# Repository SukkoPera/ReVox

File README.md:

# ReVox
ReVox is an Open Hardware sound card that adds a Digital-to-Analog Converter (DAC) to the Commodore 16, 116 and Plus/4 home computers.

## Summary
The project was born from [an idea by Spektro](https://plus4world.powweb.com/forum/46186) to get his [Covox Speech Thing](https://en.wikipedia.org/wiki/Covox_Speech_Thing) working on his Plus/4. While I was trying to help him, I found [Yeo Kheng Meng's Speech Thing reimplementation](https://github.com/yeokm1/pcb-covox-amp) and decided to derive a C16/C116/+4 cartridge from it, since it looked pretty easy and the complete board would be usable on the C16/C116 as well (Initial attempts were aimed at connecting it to the User Port, which only the Plus/4 has and which does not even feature an audio input pin).

The outcome is a a very cheap board (it can probably be built with <10€ in components) that gives the C16/C116/+4 the ability to play sound samples with good quality. It is compatible with Solder/Synergy's [Digi-Blaster](https://plus4world.powweb.com/hardware/Digi-Blaster) and thus it can be used with all the (little, to be honest) [software that supports it](https://plus4world.powweb.com/effects/Digi-Blaster_support).

## Programming
ReVox has no buffer, which means it must be fed audio samples in real-time. This is not a trivial task and existing software should be analyzed in order to learn the best techniques to do so.

Sample data must be written to the same address as the Digi-Blaster, i.e.: $FD5E or $FE9E.

## Design and Assembly Notes
The board uses a [Resistor Ladder DAC](https://en.wikipedia.org/wiki/Resistor_ladder#R%E2%80%932R_resistor_ladder_network_(digital_to_analog_conversion)) which requires a bunch of resistors of some value (R) and another bunch of exactly twice that value (2R). While the exact values used are not too critical, in order to get the best sound out of it, it is imperative that *accurate* resistors are used. Now, don't be paranoid, **1% will be more than enough** and since anything in the 1k-100k range is probably fine, you can easily find something at a decent price. For instance, I used [MFR-25FTE52-11K](https://www.mouser.it/ProductDetail/YAGEO/MFR-25FTE52-11K?qs=oAGoVhmvjhw%252BYyqfPO08%252Bg%3D%3D) and [MFR-25FTE52-22K](https://www.mouser.it/ProductDetail/YAGEO/MFR-25FTE52-22K?qs=oAGoVhmvjhy9HBN%252Bz%2FOCyQ%3D%3D): you can get 100 of each for under 4€ and those will be enough to build at least 10 boards :).

Capacitor C3 introduces a low-pass filter at the DAC output: the value I used is 1.8nF but this was chosen "by ear", not by calculations. Feel free to try different values to your liking, in the 470pF-10nF range. Note that the value also depends on those of the resistors used in the ladder, so if you change those, you will need to change this one just as well.

The audio output is automatically fed back into the computer through the EXT_AUDIO pin, so that you will hear it mixed with the sounds produced by the TED. This might need some amplification, depending on the values of the resistors used, thus the board features an amplifier with configurable gain in order to bring the volume to an acceptable level. The original design uses a TLC272 (just because I had some laying around) but any other amplifier can be used with little modifications (which are up to you). One other I tested is LMC6482, with which R17 and R18 can be set to the same value (I used the same 11k resistors I used in the ladder), as it is a rail-to-rail model.

Actually not much amplification is needed with the 11/22K resistors. In fact, the JP1 jumper on the back of the board allows to completely bypass the amplifier, just in case: set it to RAW for bypassing or to AMP otherwise.

There is also a 3.5" jack connector on the board, which allows bringing the raw output of the DAC (and low-pass filter) to external equipment. Note that when a jack is plugged in, the DAC output will no longer be redirected to the EXT_AUDIO pin.

## Testing
I suggest to use [WavePlay-SD](https://plus4world.powweb.com/software/WavePlay-SD), a great piece of software that plays music with superb quality. Enter the Setup menu with <kbd>CTRL+S</kbd> and select *INT. INTL DGB:0* using the *MOD* button.

## License
The ReVox documentation, including the design itself, is copyright &copy; SukkoPera 2023 and is licensed under the [Creative Commons Attribution-NonCommercial-ShareAlike 4.0 International License](https://creativecommons.org/licenses/by-nc-sa/4.0/).

This documentation is distributed *as is* and WITHOUT ANY EXPRESS OR IMPLIED WARRANTIES whatsoever with respect to its functionality, operability or use, including, without limitation, any implied warranties OF MERCHANTABILITY, SATISFACTORY QUALITY, FITNESS FOR A PARTICULAR PURPOSE or infringement. We expressly disclaim any liability whatsoever for any direct, indirect, consequential, incidental or special damages, including, without limitation, lost revenues, lost profits, losses resulting from business interruption or loss of data, regardless of the form of action or legal theory under which the liability may be asserted, even if advised of the possibility or likelihood of such damages.

## Support the Project
If you want to get some boards manufactured, you can get them from PCBWay through this link:

You get my gratitude and cheap, professionally-made and good quality PCBs, I get some credit that will help with this and [other projects](https://www.pcbway.com/project/member/?bmbno=72D33927-5EF6-42). You won't even have to worry about the various PCB options, it's all pre-configured for you!

Also, if you still have to register, [you can use this link](https://www.pcbway.com/setinvite.aspx?inviteid=41100) to get some bonus initial credit (and yield me some more).

You can also buy me a coffee if you want, all the money collected this way will actually go to charity:

## Thanks
* Spektro for the original idea.
* Yeo Kheng Meng for his Speech Thing reimplementation.
* MMS, BSZ and all the other folks at the [Plus/4 World Forum](https://plus4world.powweb.com/forum) for help and advice.

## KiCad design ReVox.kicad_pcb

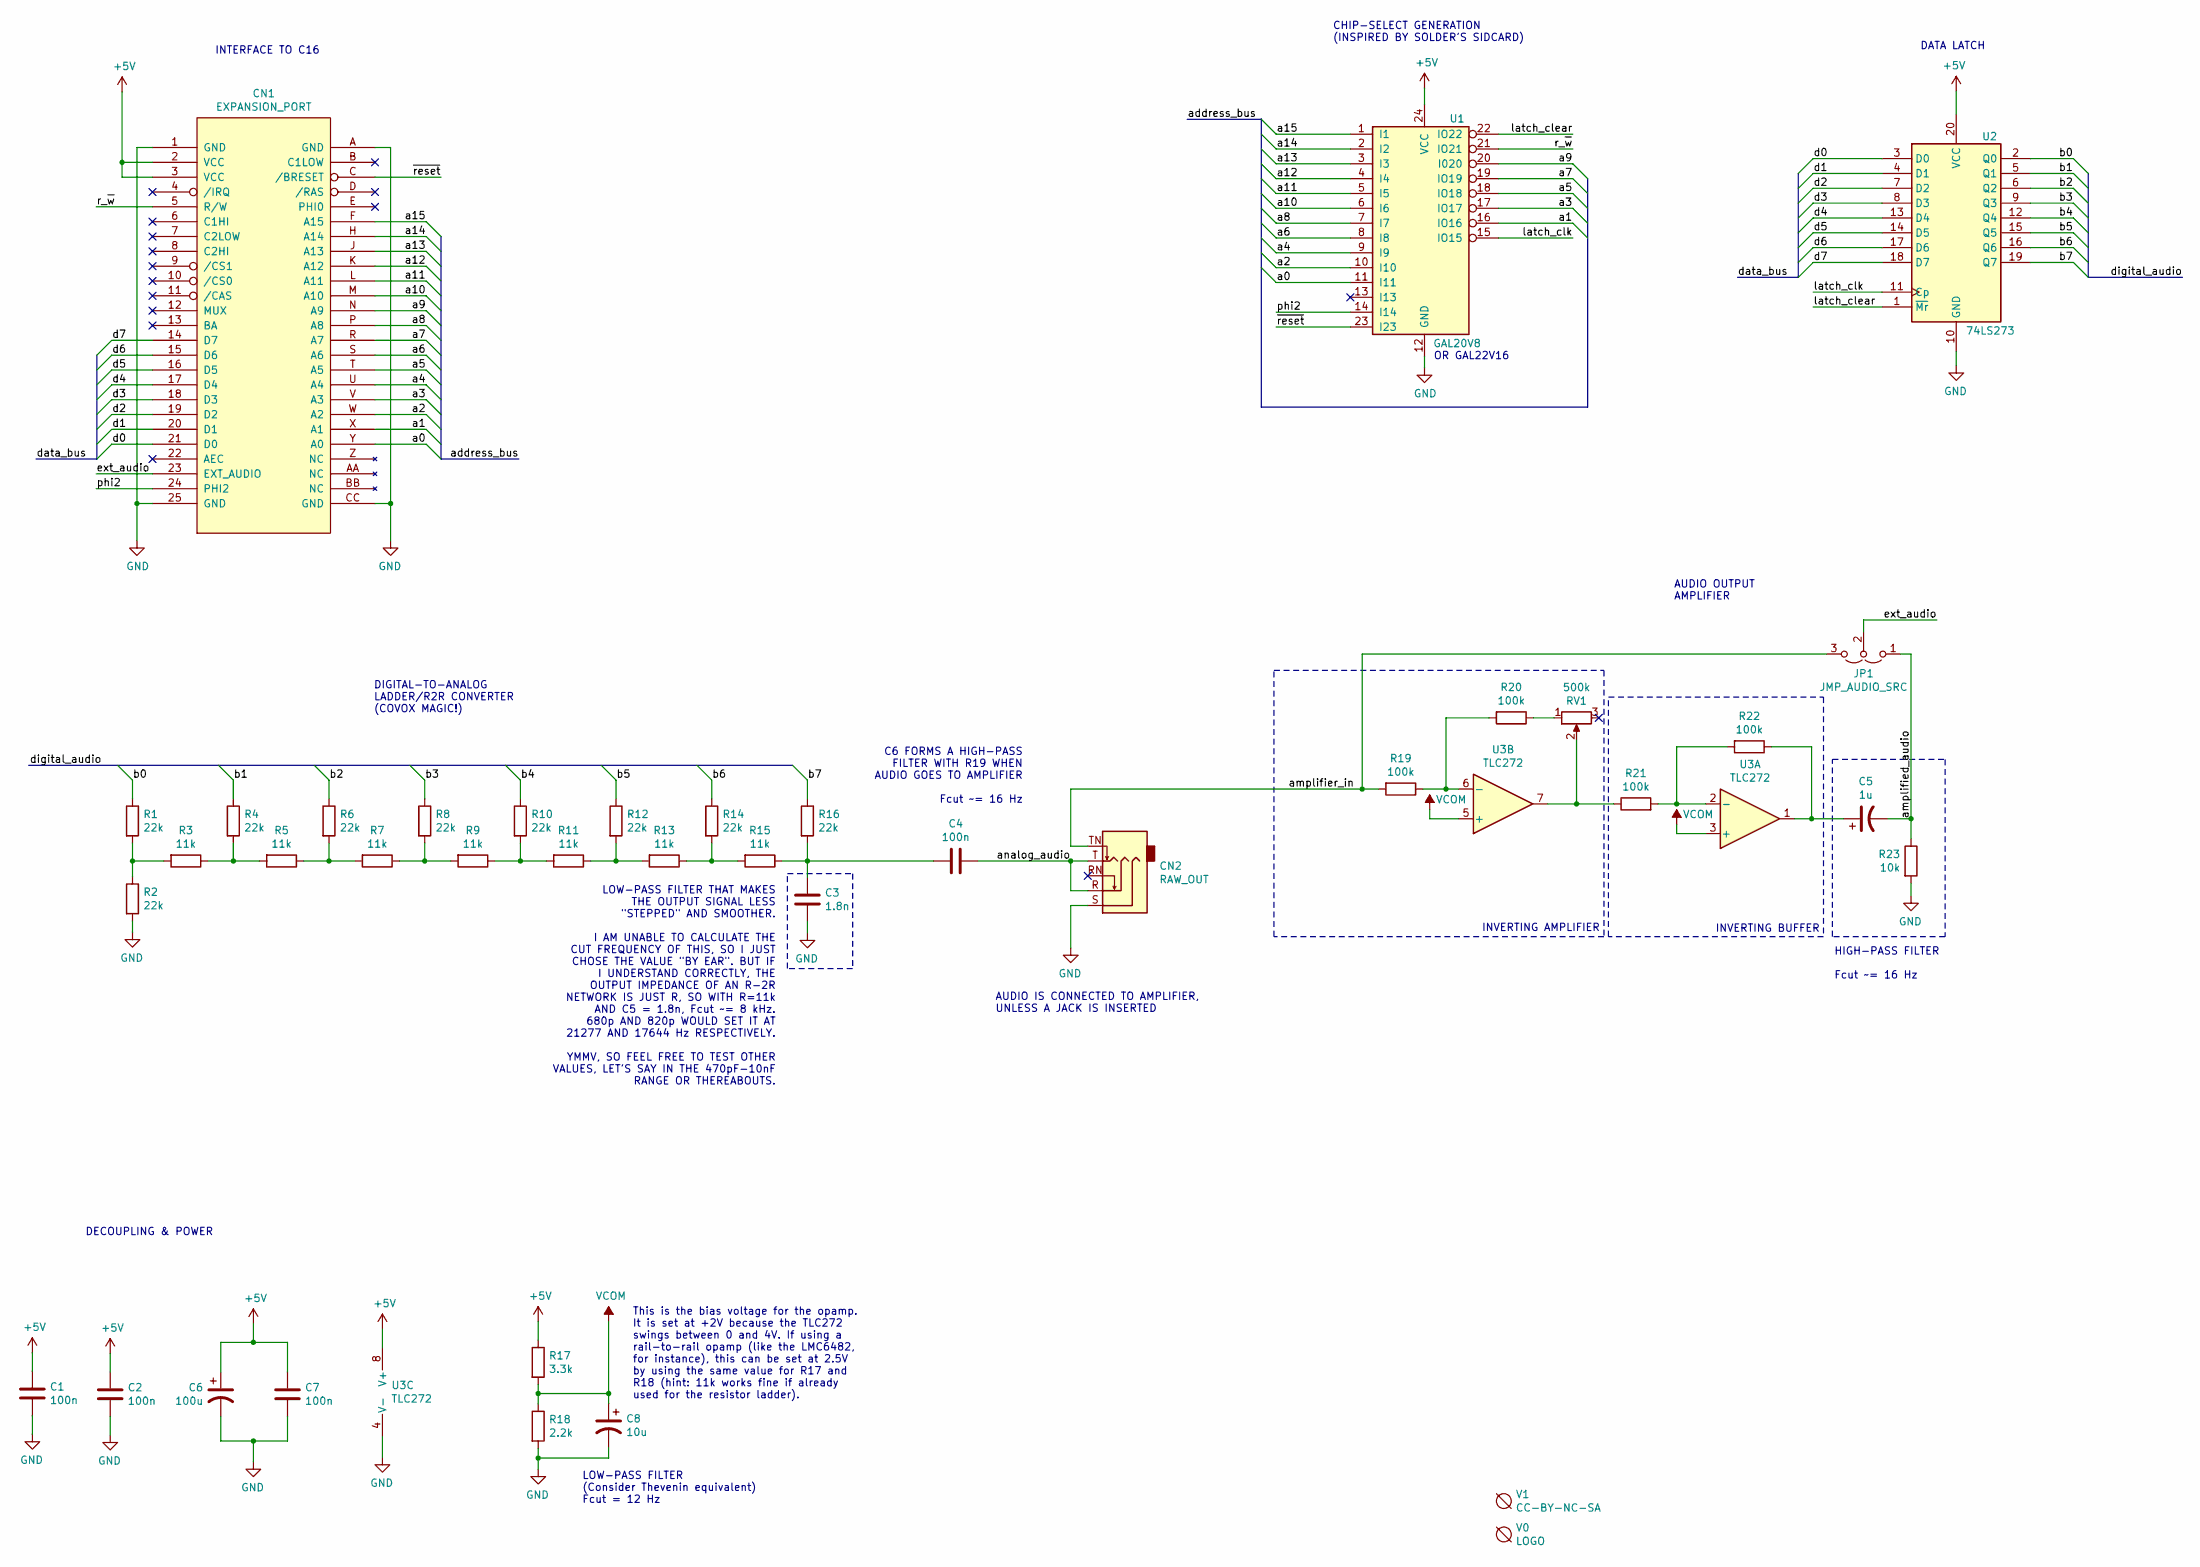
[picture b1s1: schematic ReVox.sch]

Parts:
C1, C2, C4, C7: 100n; C_Disc_D7.0mm_W2.5mm_P5.00mm; MouserPN 810-FG28X7R1H104KNT0
C3: 1.8n; C_Disc_D7.0mm_W2.5mm_P5.00mm; MouserPN 810-FG28X7R1H103KNT6
C5: 1u; CP_Radial_D5.0mm_P2.00mm; MouserPN 710-860010672005
C6: 100u; CP_Radial_D6.3mm_P2.50mm; MouserPN 710-860020573008
C8: 10u; CP_Radial_D5.0mm_P2.00mm; MouserPN 710-860010572002
CN1: EXPANSION_PORT; C16_Cart_Conn
CN2: RAW_OUT; AudioJack_SJ1-3525N; MouserPN 490-SJ1-3525N
JP1: JMP_AUDIO_SRC; SolderJumper-3_P1.3mm_Open_RoundedPad1.0x1.5mm
R1, R2, R4, R6, R8, R10, R12, R14, R16: 22k; R_Axial_DIN0207_L6.3mm_D2.5mm_P10.16mm_Horizontal; MouserPN 603-MFR-25FTE52-22K
R3, R5, R7, R9, R11, R13, R15: 11k; R_Axial_DIN0207_L6.3mm_D2.5mm_P10.16mm_Horizontal; MouserPN 603-MFR-25FTE52-11K
R17: 3.3k; R_Axial_DIN0207_L6.3mm_D2.5mm_P10.16mm_Horizontal
R18: 2.2k; R_Axial_DIN0207_L6.3mm_D2.5mm_P10.16mm_Horizontal
R19, R20, R21, R22: 100k; R_Axial_DIN0207_L6.3mm_D2.5mm_P10.16mm_Horizontal; MouserPN 603-MFR-25FTE52-11K
R23: 10k; R_Axial_DIN0207_L6.3mm_D2.5mm_P10.16mm_Horizontal; MouserPN 603-MFR-25FTE52-11K
RV1: 500k; Pot_Bourns_3306P; MouserPN 652-3306P-1-504
U1: GAL20V8; DIP-24_W7.62mm_Socket_LongPads; MouserPN 556-AF22LV10CQZ-30PU
U2: 74LS273; DIP-20_W7.62mm_Socket_LongPads; MouserPN 595-SN74HCT273N
U3: TLC272; DIP-8_W7.62mm_Socket_LongPads; MouserPN 595-TLC272BIP
V0: LOGO; logo
V1: CC-BY-NC-SA; cc_by_nc_sa

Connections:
+5V: C1.1, C2.1, C6.1, C7.1, CN1.2 (VCC), CN1.3 (VCC), R17.1, U1.24 (VCC), U2.20 (VCC), U3.8 (V+)
/a0: CN1.Y (A0), U1.11 (I11)
/a1: CN1.X (A1), U1.16 (IO16)
/a2: CN1.W (A2), U1.10 (I10)
/a3: CN1.V (A3), U1.17 (IO17)
/a4: CN1.U (A4), U1.9 (I9)
/a5: CN1.T (A5), U1.18 (IO18)
/a6: CN1.S (A6), U1.8 (I8)
/a7: CN1.R (A7), U1.19 (IO19)
/a8: CN1.P (A8), U1.7 (I7)
/a9: CN1.N (A9), U1.20 (I020)
/a10: CN1.M (A10), U1.6 (I6)
/a11: CN1.L (A11), U1.5 (I5)
/a12: CN1.K (A12), U1.4 (I4)
/a13: CN1.J (A13), U1.3 (I3)
/a14: CN1.H (A14), U1.2 (I2)
/a15: CN1.F (A15), U1.1 (I1)
/amplified_audio: C5.2, JP1.1 (A), R23.1
/amplifier_in: CN2.TN, JP1.3 (B), R19.2
/analog_audio: C4.1, CN2.R, CN2.T
/b0: R1.1, U2.2 (Q0)
/b1: R4.1, U2.5 (Q1)
/b2: R6.1, U2.6 (Q2)
/b3: R8.1, U2.9 (Q3)
/b4: R10.1, U2.12 (Q4)
/b5: R12.1, U2.15 (Q5)
/b6: R14.1, U2.16 (Q6)
/b7: R16.1, U2.19 (Q7)
/d0: CN1.21 (D0), U2.3 (D0)
/d1: CN1.20 (D1), U2.4 (D1)
/d2: CN1.19 (D2), U2.7 (D2)
/d3: CN1.18 (D3), U2.8 (D3)
/d4: CN1.17 (D4), U2.13 (D4)
/d5: CN1.16 (D5), U2.14 (D5)
/d6: CN1.15 (D6), U2.17 (D6)
/d7: CN1.14 (D7), U2.18 (D7)
/ext_audio: CN1.23 (EXT_AUDIO), JP1.2 (C)
/latch_clear: U1.22 (IO22), U2.1 (~Mr)
/latch_clk: U1.15 (IO15), U2.11 (Cp)
/phi2: CN1.24 (PHI2), U1.14 (I14)
/r_~w: CN1.5 (R/W), U1.21 (IO21)
/~reset: CN1.C (/BRESET), U1.23 (I23)
GND: C1.2, C2.2, C3.1, C6.2, C7.2, C8.2, CN1.1 (GND), CN1.25 (GND), CN1.A (GND), CN1.CC (GND), CN2.S, R2.2, R18.2, R23.2, U1.12 (GND), U2.10 (GND), U3.4 (V-)
unnamed: C3.2, C4.2, R15.1, R16.2
unnamed: C5.1, R22.1, U3.1
unnamed: R1.2, R2.1, R3.2
unnamed: R3.1, R4.2, R5.2
unnamed: R5.1, R6.2, R7.2
unnamed: R7.1, R8.2, R9.2
unnamed: R9.1, R10.2, R11.2
unnamed: R11.1, R12.2, R13.2
unnamed: R13.1, R14.2, R15.2
unnamed: R19.1, R20.2, U3.6 (-)
unnamed: R20.1, RV1.1
unnamed: R21.1, RV1.2, U3.7
unnamed: R21.2, R22.2, U3.2 (-)
VCOM: C8.1, R17.2, R18.1, U3.3 (+), U3.5 (+)

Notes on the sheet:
CHIP-SELECT GENERATION (INSPIRED BY SOLDER'S SIDCARD)
DATA LATCH
INTERFACE TO C16
DECOUPLING & POWER
OR GAL22V16
DIGITAL-TO-ANALOG LADDER/R2R CONVERTER (COVOX MAGIC!)
AUDIO IS CONNECTED TO AMPLIFIER, UNLESS A JACK IS INSERTED
INVERTING AMPLIFIER
INVERTING BUFFER
AUDIO OUTPUT AMPLIFIER
LOW-PASS FILTER (Consider Thevenin equivalent) Fcut = 12 Hz
LOW-PASS FILTER THAT MAKES THE OUTPUT SIGNAL LESS "STEPPED" AND SMOOTHER. I AM UNABLE TO CALCULATE THE CUT FREQUENCY OF THIS, SO I JUST CHOSE THE VALUE "BY EAR". BUT IF I UNDERSTAND CORRECTLY, THE OUTPUT IMPEDANCE OF AN R-2R NETWORK IS JUST R, SO WITH R=11k AND C5 = 1.8n, Fcut ~~= 8 kHz. 680p AND 8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
C6 FORMS A HIGH-PASS FILTER WITH R19 WHEN AUDIO GOES TO AMPLIFIER Fcut ~~= 16 Hz
HIGH-PASS FILTER Fcut ~~= 16 Hz
This is the bias voltage for the opamp. It is set at +2V because the TLC272 swings between 0 and 4V. If using a rail-to-rail opamp (like the LMC6482, for instance), this can be set at 2.5V by using the same value for R17 and R18 (hint: 11k works fine if already used for the resistor ladder).

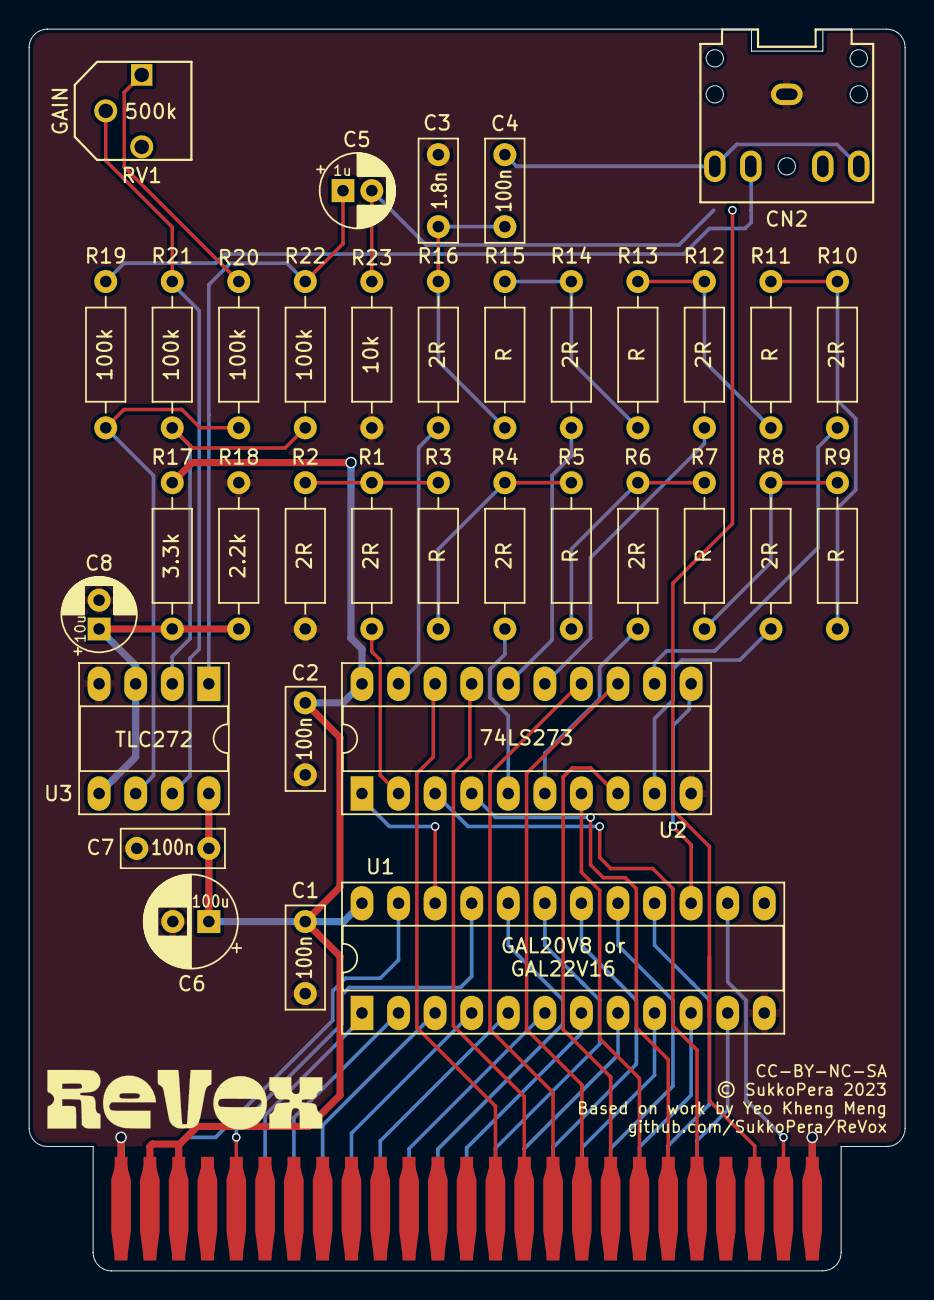
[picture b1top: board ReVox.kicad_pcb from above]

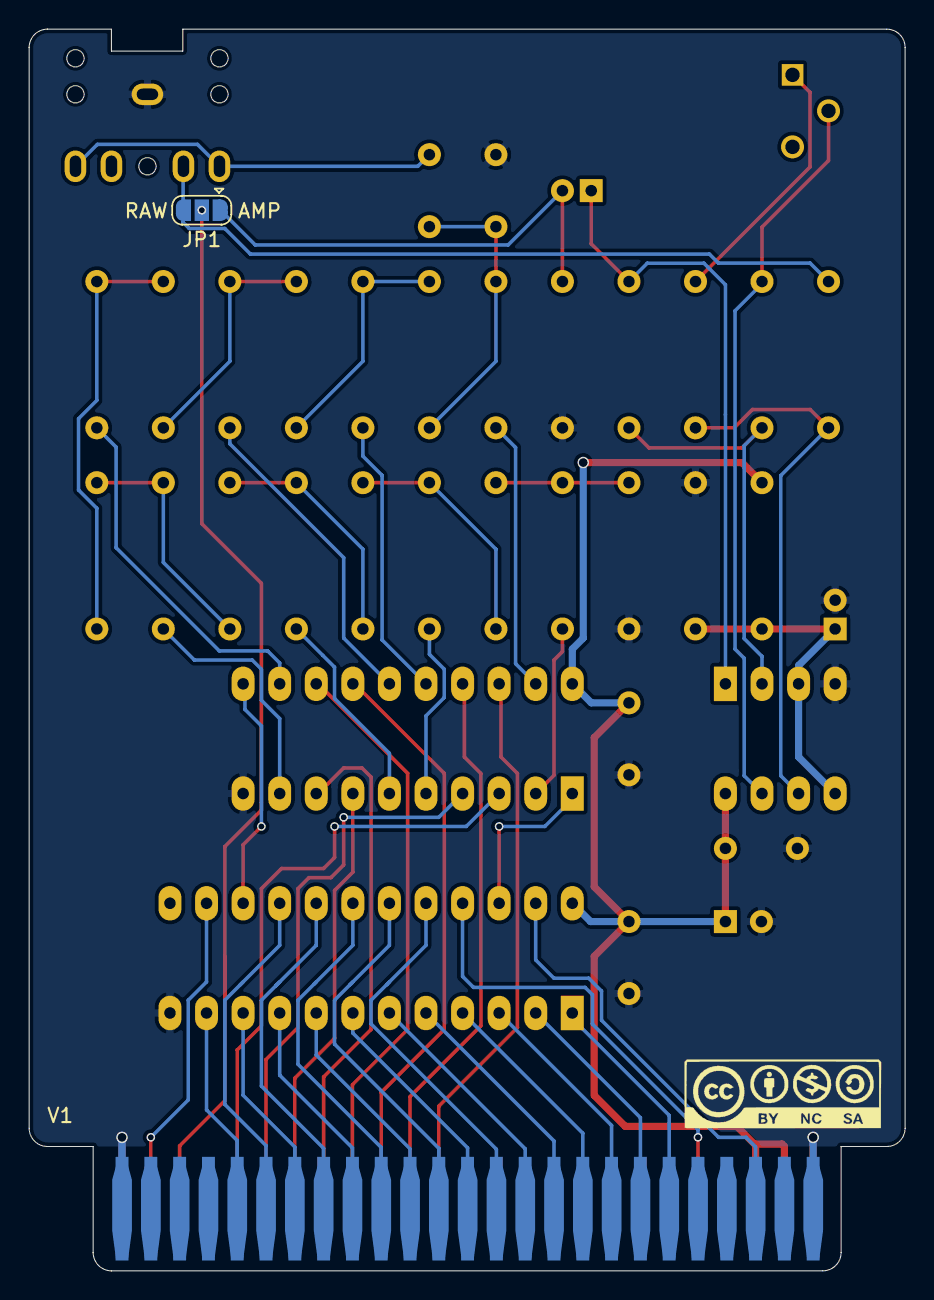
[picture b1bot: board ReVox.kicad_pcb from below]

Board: 2 copper layers, 60.8 x 86.2 mm, 40 parts (2 on the bottom side), 57 nets.

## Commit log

2023-04-02 First routing pass completed
2023-04-02 Refinements
2023-08-03 Move pots up, so that they remain accessible while the board is plugged into the machine
2023-08-03 Tidy up
2023-08-03 Final touches
2023-08-03 Final touches on silkscreen
2023-08-20 Add GAL22 equations. Note that GAL20 cannot be used with the current PCB :(
2023-08-20 Shuffle some things around so that GAL20 is usable too
2023-08-20 Add pin header with raw DAC signal, useful for testing
2023-08-20 Improve RF immunity
2023-08-21 Add P/Ns
2023-08-22 Add volume wiper series resistor
2023-08-22 Some rerouting
2023-09-05 Simpler amplifier circuit
2023-09-05 Move some stuff
2023-09-05 Routing done
2023-09-24 RV1 -> 500k
2023-10-29 Update GAL equations for V1rc2 and add GAL20 support
2023-10-29 C8 -> 1uF
2023-11-04 Add a few notes on schematics
2023-11-04 Add README
2023-11-16 Remove amplified output jack This makes the opamp oscillate and is totally unnecessary
2023-12-20 Update edge connector
2023-12-20 Update README and add renders

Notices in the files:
ReVox.kicad_pcb:
Licensed under CC BY-NC-SA 4.0
